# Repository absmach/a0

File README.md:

# 🔌 A0 Gateway

a0 is a modular **IoT gateway** built around the **ESP32-C6 (RISC-V)** platform, offering advanced wireless capabilities such as **Wi-Fi 6**, **Bluetooth 5**, and **802.15.4**. It supports multiple connectivity options including NB-IoT/LTE-M, WMBUS, and sub-GHz, enabling secure and scalable IoT deployments across smart buildings, industrial environments, and city infrastructure.

Optimized for low-power, battery-powered operation and modular expansion, A0 integrates secure communication, local storage, and multiple radio interfaces to serve as a versatile edge gateway in modern IoT ecosystems. While it includes support for Wireless and Wired M-Bus, its primary focus is on broad IoT connectivity and interoperability.

## 🌟 Features

- ⚙️ **RISC-V Architecture**: Powered by ESP32-C6 with a RISC-V core for efficiency and flexibility.
- 📡 **Advanced Wireless Connectivity**: Supports Wi-Fi 6, Bluetooth 5, and 802.15.4 for robust IoT networking.
- 🌐 **Multiple Uplink Options**: Provides NB-IoT/LTE-M for reliable data transmission.
- 🔋 **Battery-Powered Operation**: Optimized for low-power deployments with long-lasting battery support.
- 🔐 **Advanced Security**: Includes RSA-3072 secure boot, AES-128/256-XTS flash encryption, digital signature, HMAC identity protection, and hardware cryptographic accelerators for performance. Built-in Trusted Execution Environment (TEE) ensures secure software separation.
- 🛠️ **Modular Design**: Optional carrier boards adds NB-IoT/LTE-M, WMBUS, and sub-GHz radio support.
- 🔗 **Flexible IoT Connectivity**: Integrates with [Magistrala](https://github.com/absmach/magistrala) using multiple IoT protocols, including MQTT, CoAP, HTTP, and WebSockets.
- 🧩 **Zephyr RTOS Support**: Compatible with Zephyr for real-time, reliable IoT applications.
- 🖥️ **WebAssembly Runtime**: Runs lightweight, portable edge logic with WAMR (WebAssembly Micro Runtime).
- 🌀 **Propeller Orchestrator Integration**: Works with [Propeller](https://github.com/absmach/propeller) for secure, policy-driven orchestration of IoT workloads across the edge-cloud continuum.
- 📈 **Future-Ready for IoT Ecosystems**: Designed for interoperability in smart buildings, industrial IoT, and city-scale deployments.

## 🛠️ How It Works

1. **Connect & Collect**  
   Gather data from IoT sensors and devices via Wireless/Wired M-Bus, Wi-Fi, BLE, or sub-GHz radio.

2. **Process at the Edge**  
   Use the **ESP32-C6** for real-time processing or deploy **WebAssembly (Wasm)** modules with **WAMR** for flexible edge logic execution.

3. **Ensure Security**  
   Protect data and code integrity with **secure boot**, **flash encryption**, and **TEE-based isolation**, leveraging ESP32-C6 hardware security features.

4. **Transmit to IoT Platform**  
   Send processed data using **NB-IoT/LTE-M**, supporting multiple protocols (**MQTT**, **CoAP**, **HTTP**, **WebSockets**) for seamless integration with [**Magistrala**](https://github.com/absmach/magistrala).

5. **Orchestrate & Scale**  
   Integrate with the [**Propeller Orchestrator**](https://github.com/absmach/propeller) for policy-driven deployment and orchestration of workloads across the edge-cloud continuum.

6. **Manage Remotely**  
   Perform **OTA updates**, monitor device health, and manage configurations through connected IoT management tools.

## 📖 Documentation

For setup instructions, pinouts, and integration guides, see the full documentation:  
🔗 [A0 Documentation](https://www.absmach.eu/docs/hardware/s1-gateway/)

## 💡 Use Cases

- 🏢 **Smart Buildings**: Connect heat and water meters via Wireless M-Bus for real-time monitoring.
- 🏭 **Industrial IoT**: Collect and transmit sensor data in secure and bandwidth-constrained environments.
- 🌍 **Smart Cities**: Enable large-scale metering infrastructure with NB-IoT and sub-GHz connectivity.
- 🔐 **Secure Data Acquisition**: Ensure encrypted communication from edge devices to the cloud.

## 🔧 Hardware Highlights

The system consists of a **base board (A0)** with plug-in **expansion modules**:

- **A0 Base Board** ([a0/](a0/README.md)):
  - MCU: **ESP32-C6** module (RISC-V architecture)
  - Connectivity: **Wi-Fi 6**, **Bluetooth 5**, **IEEE 802.15.4**
  - Security: **Secure Boot**, **Flash Encryption**, **TEE**, Hardware Crypto Accelerators
  - Power: **USB-C**, external power supply, or **battery** (with charging support)
  - Expansion: **2 module slots — BUS1 and BUS2** — for plug-in connectivity modules

- **Expansion Modules** (plug into BUS1/BUS2):
  - [**SIM7080G**](modules/sim7080g/README.md): NB-IoT / LTE-M cellular uplink + GNSS
  - [**WMBUS**](modules/wmbus/README.md): Wireless M-Bus metering radio
  - [**E07-400M10S**](modules/E07400M10S/README.md): Sub-GHz radio module (400 MHz, 10 dBm)

## 🤝 Contributing

Contributions are welcome! Please check the [CONTRIBUTING.md](#) for details on how to get started.

## 📜 License

A0 is licensed under the **Apache-2.0 License**. See the [LICENSE](LICENSE) file for more details.

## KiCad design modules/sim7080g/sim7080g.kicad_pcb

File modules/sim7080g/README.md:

# SIM7080G Module

A plug-in expansion module for the [A0 base board](../../a0/README.md) based on the **SIMCom SIM7080G**.

## Overview

The SIM7080G provides **NB-IoT / LTE-M (Cat-M)** cellular connectivity plus **GNSS** positioning. Plug it into one of the A0 base board's expansion slots (**BUS1** or **BUS2**) to add a reliable cellular uplink for NB-IoT and LTE-M deployments.

## Key Features

- **Cellular**: NB-IoT and LTE-M (Cat-M) uplink
- **GNSS**: GPS/GLONASS/BeiDou/Galileo positioning
- **Interface**: connects to the ESP32-C6 over UART via the expansion bus
- **Power**: supplied from the expansion bus

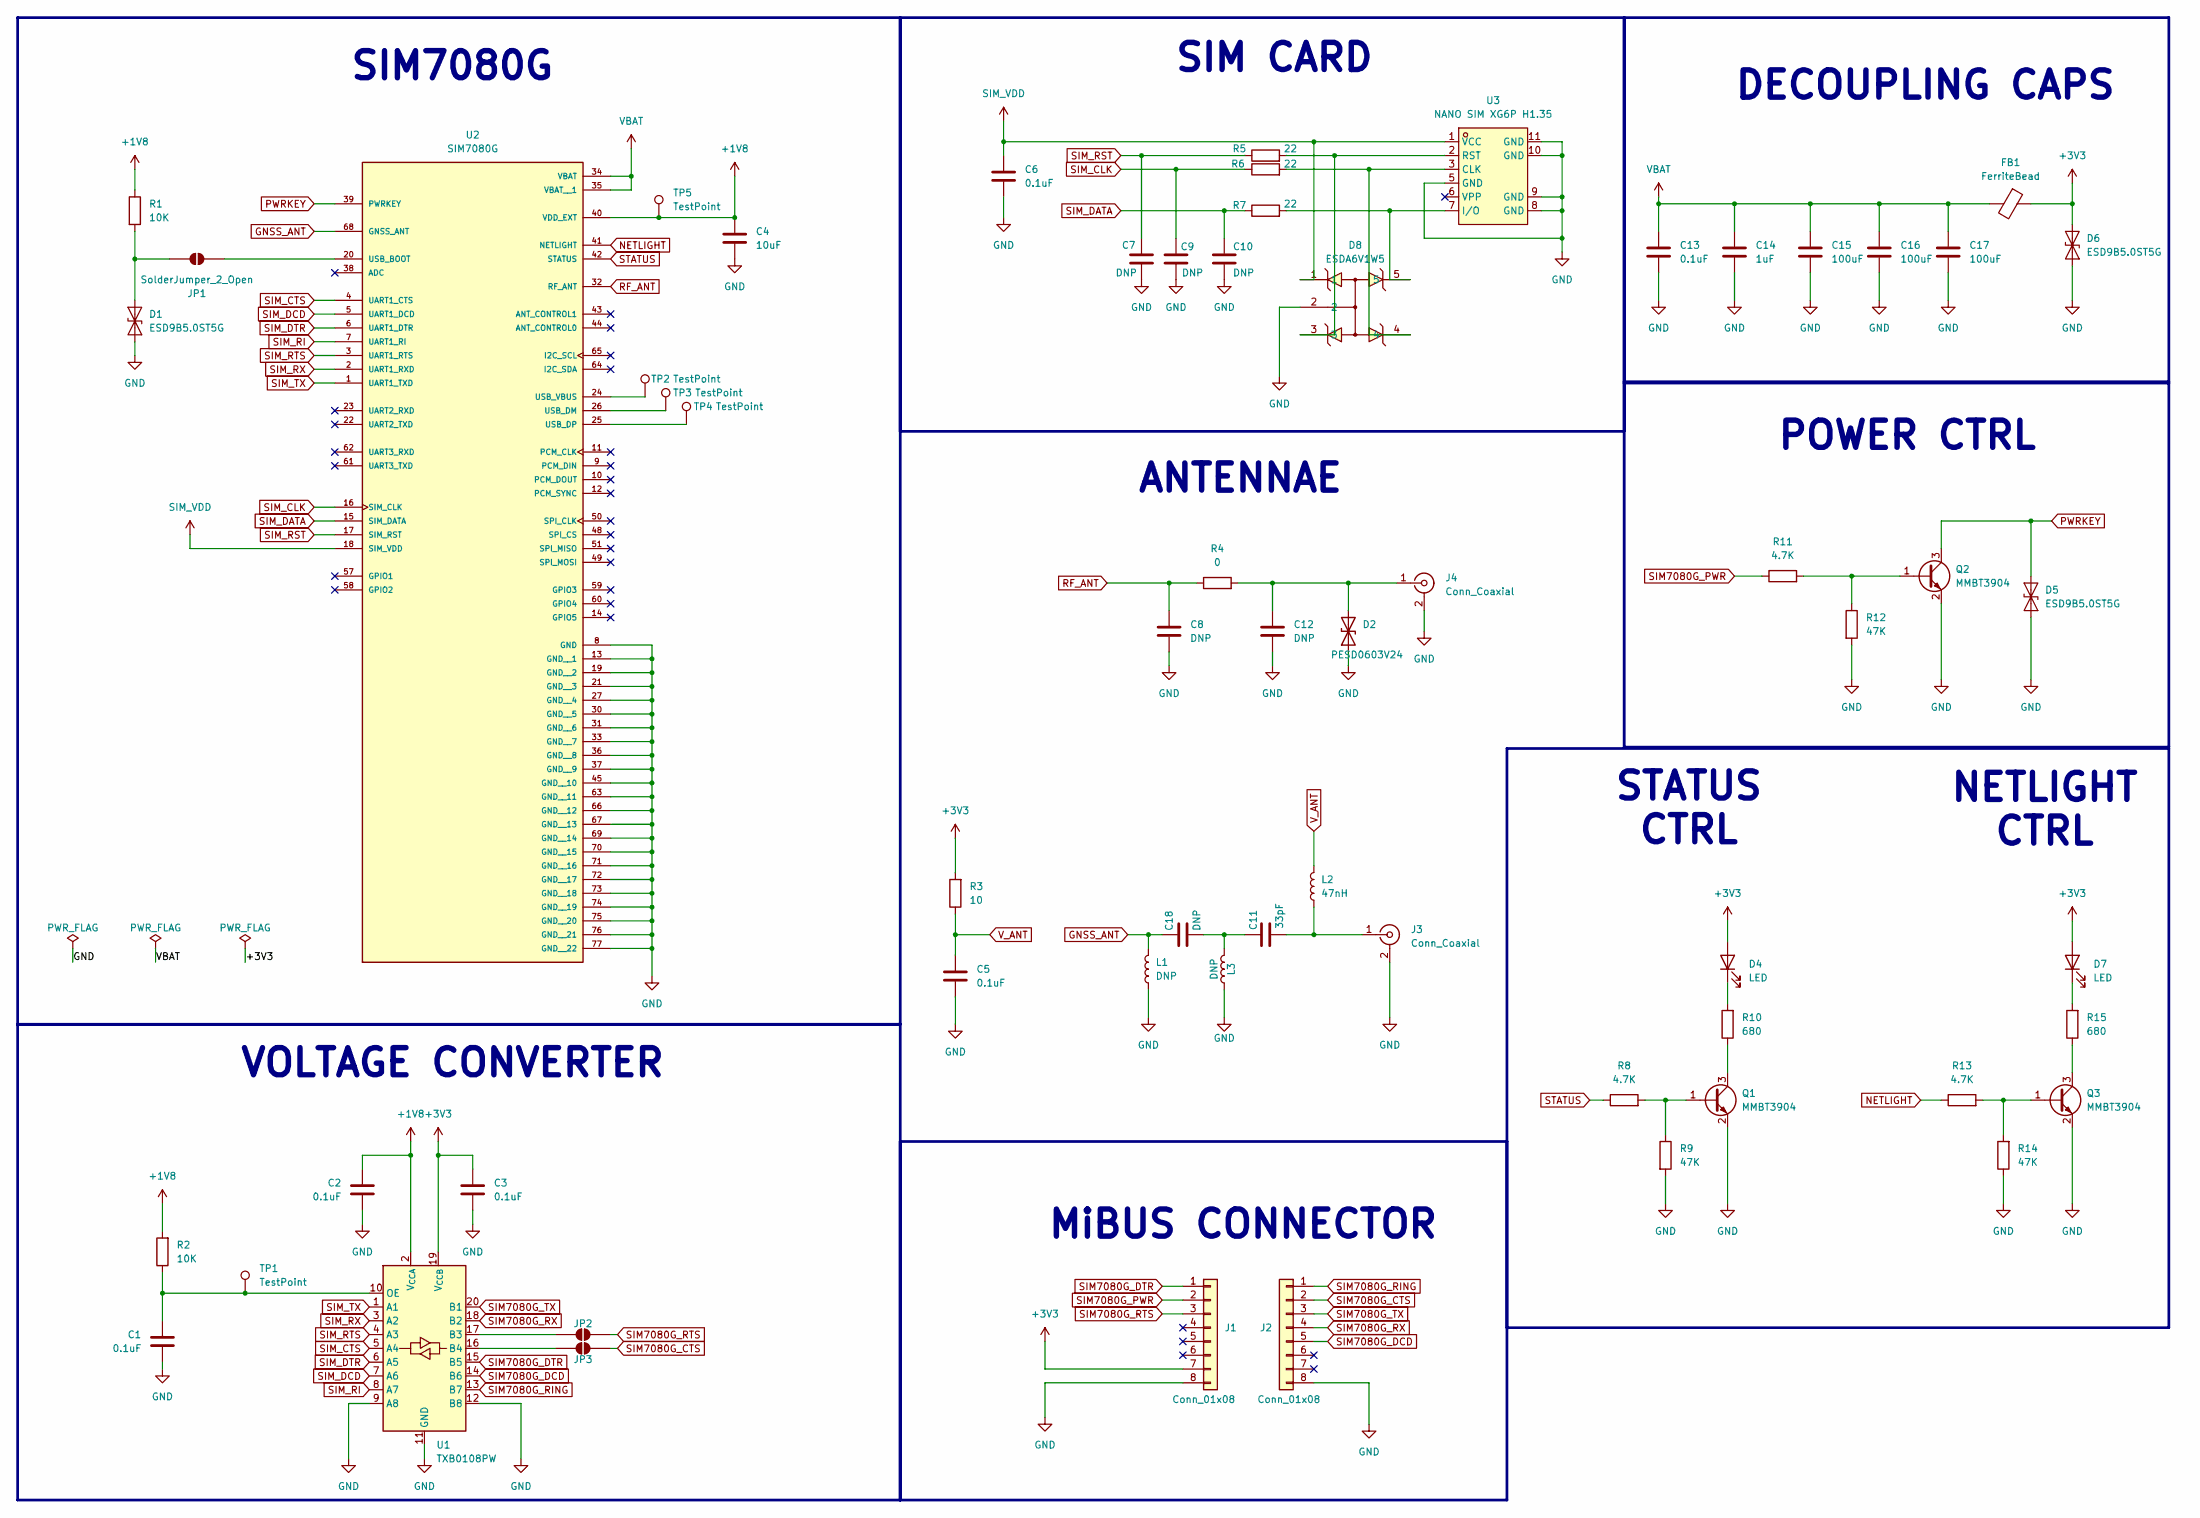
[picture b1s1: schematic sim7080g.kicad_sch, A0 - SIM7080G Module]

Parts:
C1, C2, C3, C5, C6, C13: 0.1uF; C_0805_2012Metric; JLCPCB C49678
C4: 10uF; C_0805_2012Metric; JLCPCB C15850
C7, C9, C10: DNP; C_0805_2012Metric; JLCPCB C1804
C8, C12: DNP; C_0402_1005Metric; JLCPCB C15008
C11: 33pF; C_0402_1005Metric; JLCPCB C1562
C14: 1uF; C_0805_2012Metric; JLCPCB C28323
C15, C16, C17: 100uF; C_1206_3216Metric; JLCPCB C15008
C18: DNP; C_0402_1005Metric
D1, D5, D6: ESD9B5.0ST5G; D_SOD-923; JLCPCB C111566
D2: PESD0603V24; D_0603_1608Metric; JLCPCB C19626259
D4, D7: LED; LED_0805_2012Metric; JLCPCB C965816
D8: ESDA6V1W5; C48677; MPN ESDA6V1W5; LCSC Part C48677
FB1: FerriteBead; L_0805_2012Metric; JLCPCB C56066
J1, J2: Conn_01x08; PinHeader_1x08_P2.54mm_Vertical; JLCPCB C492407
J3, J4: Conn_Coaxial; U.FL_Hirose_U.FL-R-SMT-1_Vertical; JLCPCB C88374
JP1, JP2, JP3: SolderJumper_2_Open; SolderJumper-2_P1.3mm_Open_RoundedPad1.0x1.5mm
L1, L3: DNP; L_0402_1005Metric
L2: 47nH; L_0402_1005Metric; JLCPCB C192855
Q1, Q2, Q3: MMBT3904; SOT-23; JLCPCB C20526
R1: 10K; R_0805_2012Metric; JLCPCB C17414
R2: 10K; R_0805_2012Metric; JLCPCB C17408
R3: 10; R_0805_2012Metric; JLCPCB C17415
R4: 0; R_0402_1005Metric; JLCPCB C17168
R5, R6, R7: 22; R_0805_2012Metric; JLCPCB C17561
R8, R11, R13: 4.7K; R_0805_2012Metric; JLCPCB C17673
R9, R12, R14: 47K; R_0805_2012Metric; JLCPCB C17713
R10, R15: 680; R_0805_2012Metric; JLCPCB C17798
TP1, TP2, TP3, TP4, TP5: TestPoint; TestPoint_Pad_1.0x1.0mm
U1: TXB0108PW; TSSOP-20_4.4x6.5mm_P0.65mm
U2: SIM7080G; PARTREV 1.04; JLCPCB C2943992
U3: NANO SIM XG6P H1.35; SIM-SMD_NANO-SIM; LCSC Part C7529386

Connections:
+1V8: C2.2, C4.2, R1.1, R2.2, TP5.1 (1_1), U1.2 (V_{CCA}), U2.40 (VDD_EXT)
+3V3: C3.2, D4.2 (A), D6.2 (A2), D7.2 (A), FB1.1, J1.7, R3.2, U1.19 (V_{CCB})
GND: C1.1, C2.1, C3.1, C4.1, C5.1, C6.1, C7.1, C8.2, C9.1, C10.1, C12.2, C13.1, C14.2, C15.2, C16.2, C17.2, D1.1 (A1), D2.1 (A1), D5.1 (A1), D6.1 (A1), D8.2, J1.8, J2.8, J3.2 (Ext), J4.2 (Ext), L1.1, L3.1, Q1.2 (E), Q2.2 (E), Q3.2 (E), R9.2, R12.2, R14.1, U1.9 (A8), U1.11 (GND), U1.12 (B8), U2.8 (GND), U2.13 (GND__1), U2.19 (GND__2), U2.21 (GND__3), U2.27 (GND__4), U2.30 (GND__5), U2.31 (GND__6), U2.33 (GND__7), U2.36 (GND__8), U2.37 (GND__9), U2.45 (GND__10), U2.63 (GND__11), U2.66 (GND__12), U2.67 (GND__13), U2.69 (GND__14), U2.70 (GND__15), U2.71 (GND__16), U2.72 (GND__17), U2.73 (GND__18), U2.74 (GND__19), U2.75 (GND__20), U2.76 (GND__21), U2.77 (GND__22), U3.5 (GND), U3.8 (GND), U3.9 (GND), U3.10 (GND), U3.11 (GND)
GNSS_ANT: C11.2, C18.1, C18.2, L1.2, L3.2, U2.68 (GNSS_ANT)
NETLIGHT: R13.1, U2.41 (NETLIGHT)
unnamed: D1.2 (A2), JP1.1 (A), R1.2
unnamed: C12.1, D2.2 (A2), J4.1 (In), R4.2
unnamed: D4.1 (K), R10.2
unnamed: D7.1 (K), R15.2
unnamed: C11.1, J3.1 (In), L2.1
unnamed: JP1.2 (B), U2.20 (USB_BOOT)
unnamed: JP2.1 (A), U1.17 (B3)
unnamed: JP3.1 (A), U1.16 (B4)
unnamed: Q1.1 (B), R8.2, R9.1
unnamed: Q1.3 (C), R10.1
unnamed: Q2.1 (B), R11.2, R12.1
unnamed: Q3.1 (B), R13.2, R14.2
unnamed: Q3.3 (C), R15.1
unnamed: C1.2, R2.1, TP1.1 (1_1), U1.10 (OE)
unnamed: TP3.1 (1_1), U2.26 (USB_DM)
unnamed: TP4.1 (1_1), U2.25 (USB_DP)
unnamed: TP2.1 (1_1), U2.24 (USB_VBUS)
unnamed: D8.4, R6.2, U3.3 (CLK)
unnamed: D8.5, R7.2, U3.7 (I/O)
unnamed: D8.3, R5.2, U3.2 (RST)
PWRKEY: D5.2 (A2), Q2.3 (C), U2.39 (PWRKEY)
RF_ANT: C8.1, R4.1, U2.32 (RF_ANT)
SIM7080G_CTS: J2.2, JP3.2 (B)
SIM7080G_DCD: J2.5, U1.14 (B6)
SIM7080G_DTR: J1.1, U1.15 (B5)
SIM7080G_PWR: J1.2, R11.1
SIM7080G_RING: J2.1, U1.13 (B7)
SIM7080G_RTS: J1.3, JP2.2 (B)
SIM7080G_RX: J2.4, U1.18 (B2)
SIM7080G_TX: J2.3, U1.20 (B1)
SIM_CLK: C9.2, R6.1, U2.16 (SIM_CLK)
SIM_CTS: U1.5 (A4), U2.4 (UART1_CTS)
SIM_DATA: C10.2, R7.1, U2.15 (SIM_DATA)
SIM_DCD: U1.7 (A6), U2.5 (UART1_DCD)
SIM_DTR: U1.6 (A5), U2.6 (UART1_DTR)
SIM_RI: U1.8 (A7), U2.7 (UART1_RI)
SIM_RST: C7.2, R5.1, U2.17 (SIM_RST)
SIM_RTS: U1.4 (A3), U2.3 (UART1_RTS)
SIM_RX: U1.3 (A2), U2.2 (UART1_RXD)
SIM_TX: U1.1 (A1), U2.1 (UART1_TXD)
SIM_VDD: C6.2, D8.1, U2.18 (SIM_VDD), U3.1 (VCC)
STATUS: R8.1, U2.42 (STATUS)
VBAT: C13.2, C14.1, C15.1, C16.1, C17.1, FB1.2, U2.34 (VBAT), U2.35 (VBAT__1)
V_ANT: C5.2, L2.2, R3.1

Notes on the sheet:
VOLTAGE CONVERTER
DECOUPLING CAPS
SIM CARD
SIM7080G
ANTENNAE
STATUS CTRL
NETLIGHT CTRL
MiBUS CONNECTOR
POWER CTRL

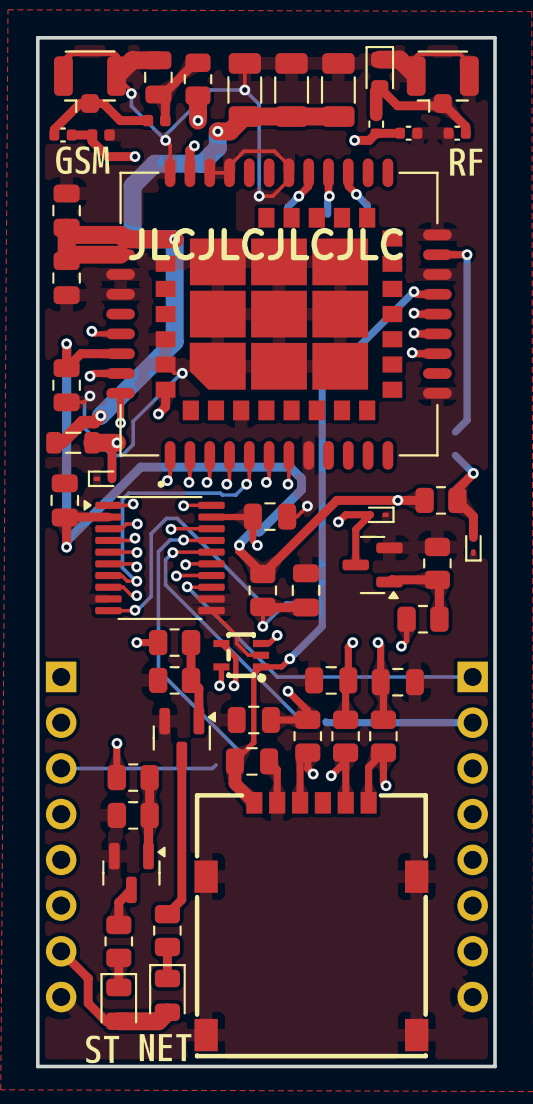
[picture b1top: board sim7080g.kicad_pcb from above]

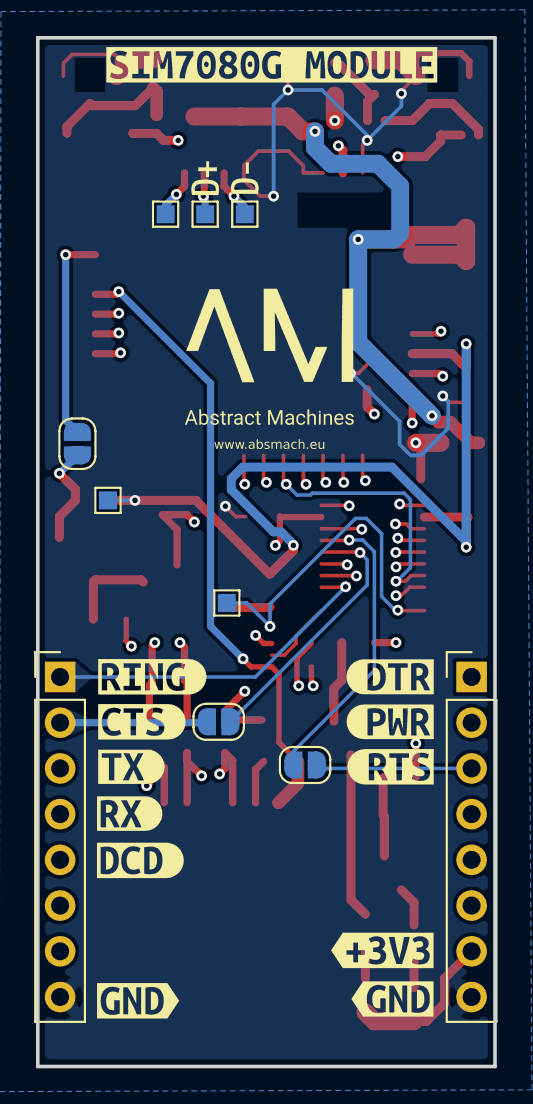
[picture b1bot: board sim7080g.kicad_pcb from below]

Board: 4 copper layers, 25.4 x 57.2 mm, 78 parts (24 on the bottom side), 49 nets.

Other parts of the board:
kibuzzard-6A58AA2C: G***; kibuzzard-6A58AA2C
kibuzzard-6A58AA08: G***; kibuzzard-6A58AA08
kibuzzard-6A58AA80: G***; kibuzzard-6A58AA80
kibuzzard-6A58AA90: G***; kibuzzard-6A58AA90
kibuzzard-6A58AAA8: G***; kibuzzard-6A58AAA8
kibuzzard-6A58AAC0: G***; kibuzzard-6A58AAC0
kibuzzard-6A58AAD1: G***; kibuzzard-6A58AAD1
kibuzzard-6A58ABB3: G***; kibuzzard-6A58ABB3
kibuzzard-6A58ABC2: G***; kibuzzard-6A58ABC2
kibuzzard-6A58ABCC: G***; kibuzzard-6A58ABCC
kibuzzard-6A58ABD9: G***; kibuzzard-6A58ABD9
kibuzzard-6A58ABE5: G***; kibuzzard-6A58ABE5
kibuzzard-6A58ADF5: G***; kibuzzard-6A58ADF5
kibuzzard-6AA2AF52: G***; kibuzzard-6AA2AF52
kibuzzard-6AA2C0AA: G***; kibuzzard-6AA2C0AA
kibuzzard-6AA2C081: G***; kibuzzard-6AA2C081
kibuzzard-6AA2C170: G***; kibuzzard-6AA2C170
kibuzzard-6AA2C182: G***; kibuzzard-6AA2C182

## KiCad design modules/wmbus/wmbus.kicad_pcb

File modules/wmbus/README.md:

# WMBUS Module

A plug-in expansion module for the [A0 base board](../../a0/README.md) implementing **Wireless M-Bus (EN 13757-4)**.

## Overview

The WMBUS module adds a Wireless M-Bus radio for reading utility meters (heat, water, gas, electricity). Plug it into one of the A0 base board's expansion slots (**BUS1** or **BUS2**) to enable smart metering deployments.

## Key Features

- **Wireless M-Bus (EN 13757-4)** communication
- Connects to the ESP32-C6 over the expansion bus
- Powered from the expansion bus

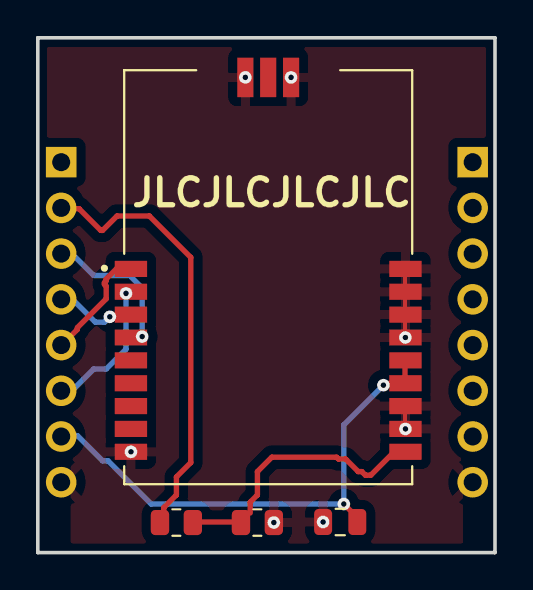
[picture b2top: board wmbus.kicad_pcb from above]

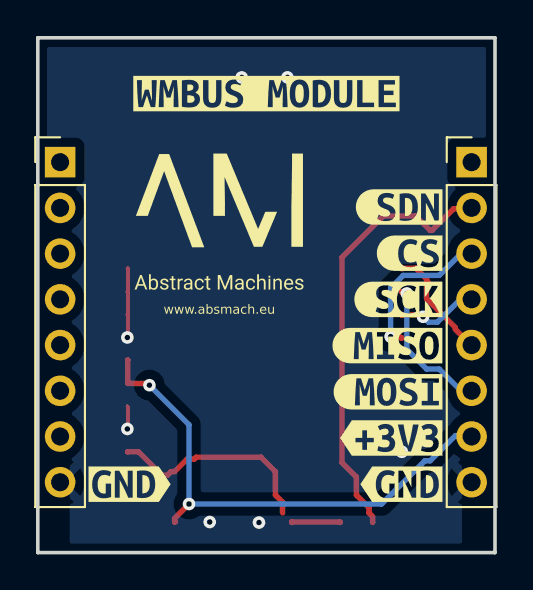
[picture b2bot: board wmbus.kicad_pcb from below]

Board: 2 copper layers, 25.4 x 28.6 mm, 15 parts (11 on the bottom side), 8 nets.

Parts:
C1: 0.1uF; C_0805_2012Metric
J1, J2: Conn_01x08; PinHeader_1x08_P2.54mm_Vertical
R1: 100; R_0805_2012Metric
R2: 10K; R_0805_2012Metric
U2: RC-S2LP-868
kibuzzard-6A563B7D: G***; kibuzzard-6A563B7D
kibuzzard-6A563B31: G***; kibuzzard-6A563B31
kibuzzard-6A563B41: G***; kibuzzard-6A563B41
kibuzzard-6A563B50: G***; kibuzzard-6A563B50
kibuzzard-6A563B65: G***; kibuzzard-6A563B65
kibuzzard-6A563B71: G***; kibuzzard-6A563B71
kibuzzard-6A563B88: G***; kibuzzard-6A563B88
kibuzzard-6A563B96: G***; kibuzzard-6A563B96
kibuzzard-6A563BEF: G***; kibuzzard-6A563BEF

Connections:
+3V3: C1.1, J1.7, U2.13 (VCC), U2.14 (VCC)
CS: J1.3, U2.4 (CSN)
GND: C1.2, J1.8, J2.8, R2.2, U2.9 (GND), U2.11 (GND), U2.12 (GND), U2.15 (GND), U2.16 (GND), U2.17 (GND), U2.18 (GND), U2.19 (GND), U2.21 (GND)
MISO: J1.5, U2.1 (SDO)
MOSI: J1.6, U2.2 (SDI)
unnamed: R1.2, R2.1, U2.10 (SDN)
SCK: J1.4, U2.3 (SCLK)
SDN: J1.2, R1.1

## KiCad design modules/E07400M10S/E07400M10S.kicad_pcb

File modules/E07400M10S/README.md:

# E07-400M10S Module

A plug-in expansion module for the [A0 base board](../../a0/README.md) based on the **Ebyte E07-400M10S** sub-GHz radio module.

## Overview

The E07-400M10S is a compact sub-GHz (400 MHz) RF transceiver module with 10 dBm output. Plug it into one of the A0 base board's expansion slots (**BUS1** or **BUS2**) to add low-power, long-range sub-GHz connectivity for private sensor networks and IEEE 802.15.4-style links.

## Key Features

- **Sub-GHz radio**: 400 MHz band, 10 dBm output power
- **Low power**: suited to battery-powered operation
- **Interface**: SPI / UART over the expansion bus
- **Power**: supplied from the expansion bus

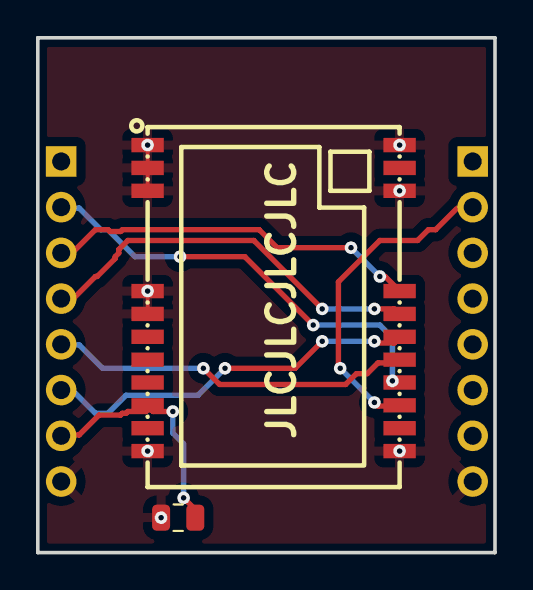
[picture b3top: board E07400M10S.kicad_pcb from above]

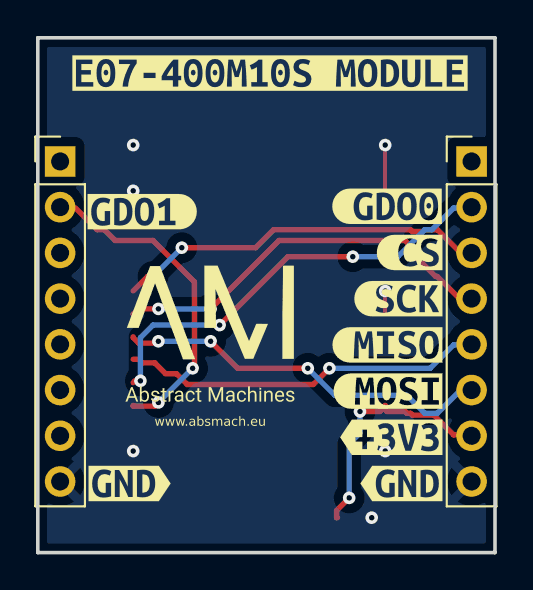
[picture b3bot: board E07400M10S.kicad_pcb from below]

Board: 2 copper layers, 25.4 x 28.6 mm, 14 parts (12 on the bottom side), 8 nets.

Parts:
C1: 0.1uF; C_0805_2012Metric
J1, J2: Conn_01x08; PinHeader_1x08_P2.54mm_Vertical
U1: E07-400M10S; C2965513
kibuzzard-6A5A4D23: G***; kibuzzard-6A5A4D23
kibuzzard-6A5A4D79: G***; kibuzzard-6A5A4D79
kibuzzard-6A5A4D90: G***; kibuzzard-6A5A4D90
kibuzzard-6A563B7D: G***; kibuzzard-6A563B7D
kibuzzard-6A563B41: G***; kibuzzard-6A563B41
kibuzzard-6A563B50: G***; kibuzzard-6A563B50
kibuzzard-6A563B65: G***; kibuzzard-6A563B65
kibuzzard-6A563B71: G***; kibuzzard-6A563B71
kibuzzard-6A563B88: G***; kibuzzard-6A563B88
kibuzzard-6A563B96: G***; kibuzzard-6A563B96

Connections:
+3V3: C1.1, J1.7, U1.9 (VCC)
CS: J1.3, U1.19 (CSN)
GDO0: J1.2, U1.15 (GD00)
GDO1: J2.2, U1.14 (GD02)
GND: C1.2, J1.8, J2.8, U1.1 (GND), U1.2 (GND), U1.3 (GND), U1.4 (GND), U1.5 (GND), U1.11 (GND), U1.12 (GND), U1.20 (GND), U1.22 (GND)
MISO: J1.5, U1.16 (MISO/GD01)
MOSI: J1.6, U1.17 (MOSI)
SCK: J1.4, U1.18 (SCK)

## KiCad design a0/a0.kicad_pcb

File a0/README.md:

# A0 Base Board

**A0** is the base board of the modular A0 IoT gateway, built around an **ESP32-C6 module** (RISC-V, Wi-Fi 6, Bluetooth 5, IEEE 802.15.4).

## About the ESP32-C6

The ESP32-C6 is Espressif's first Wi-Fi 6 SoC, integrating **2.4 GHz Wi-Fi 6 (802.11ax)**, **Bluetooth 5 (LE)** and **IEEE 802.15.4** (Thread/Zigbee) radio connectivity in a single low-power chip ([product page](https://www.espressif.com/en/products/socs/esp32-c6)).

| Spec            | Details                                                                                                                                                                                                                                                        |
| --------------- | -------------------------------------------------------------------------------------------------------------------------------------------------------------------------------------------------------------------------------------------------------------- |
| **CPU**         | High-performance 32-bit RISC-V core, up to **160 MHz**, plus a low-power (LP) 32-bit RISC-V core, up to **20 MHz**                                                                                                                                             |
| **Memory**      | 320 KB ROM, 512 KB SRAM, external flash                                                                                                                                                                                                                        |
| **Wireless**    | 2.4 GHz Wi-Fi 6 (802.11ax, 20 MHz) with 802.11 b/g/n (20/40 MHz) backward compatibility; OFDMA up/downlink, downlink MU-MIMO, Target Wake Time (TWT); Bluetooth 5 LE with coded PHY long-range and 2 Mbps high-throughput PHY; IEEE 802.15.4 for Thread/Zigbee |
| **GPIO**        | 30 (QFN40) or 22 (QFN32) programmable GPIOs                                                                                                                                                                                                                    |
| **Peripherals** | SPI, UART, I2C, I2S, RMT, TWAI, PWM, SDIO, Motor Control PWM, 12-bit ADC, temperature sensor                                                                                                                                                                   |
| **Security**    | RSA-3072 secure boot, AES-128/256-XTS flash encryption, digital signature and HMAC peripherals, hardware cryptographic accelerators, Trusted Execution Environment (TEE) for privilege/software separation                                                     |
| **Software**    | Open-source ESP-IDF; ESP-Hosted / ESP-AT for co-processor use; ESP RainMaker; Zephyr support                                                                                                                                                                   |

Wi-Fi 6 features (OFDMA, MU-MIMO, TWT) deliver low latency and long battery life even in congested RF environments, while combined Wi-Fi + BLE + 802.15.4 support makes it a natural fit for Matter end-point devices, Thread Border Routers, and Zigbee bridges.

## Overview

A0 provides everything needed to power and run the gateway, while pushing all radio/cellular connectivity onto removable expansion modules:

- **ESP32-C6 module on top** — main compute + Wi-Fi/BLE/802.15.4 connectivity, with hardware secure boot, flash encryption, and a TEE.
- **Power**:
  - USB-C power input
  - External power supply input
  - Battery support (with charging)
- **Expansion**: two module slots, **BUS1** and **BUS2**, where any of the following modules can be plugged in:
  - [SIM7080G](../modules/sim7080g/README.md) — NB-IoT/LTE-M cellular + GNSS
  - [WMBUS](../modules/wmbus/README.md) — Wireless M-Bus radio
  - [E07-400M10S](../modules/E07400M10S/README.md) — Sub-GHz radio (400 MHz, 10 dBm)

## Manufacturing

Gerber and assembly outputs are in [`jlcpcb/`](jlcpcb/) (`gerber/` and `production_files/`).

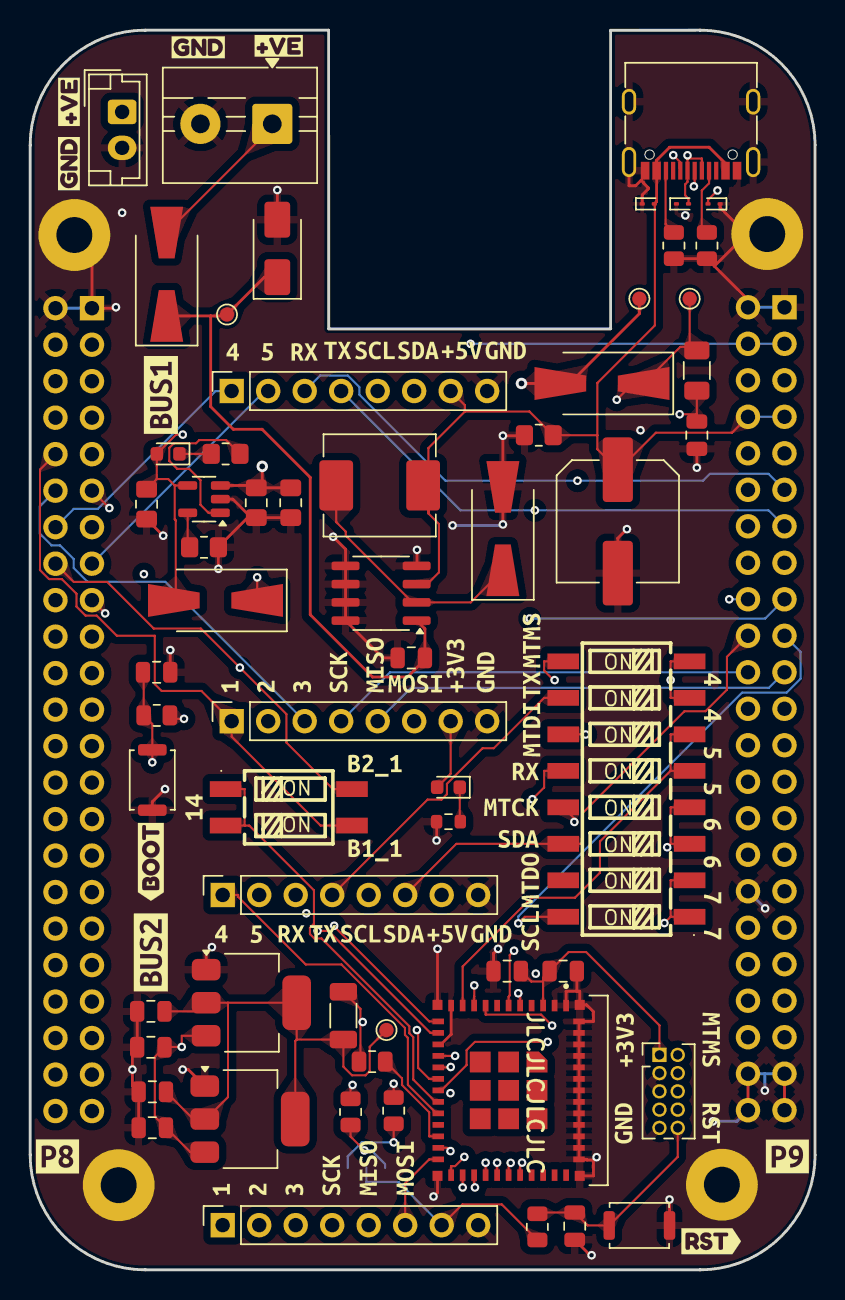
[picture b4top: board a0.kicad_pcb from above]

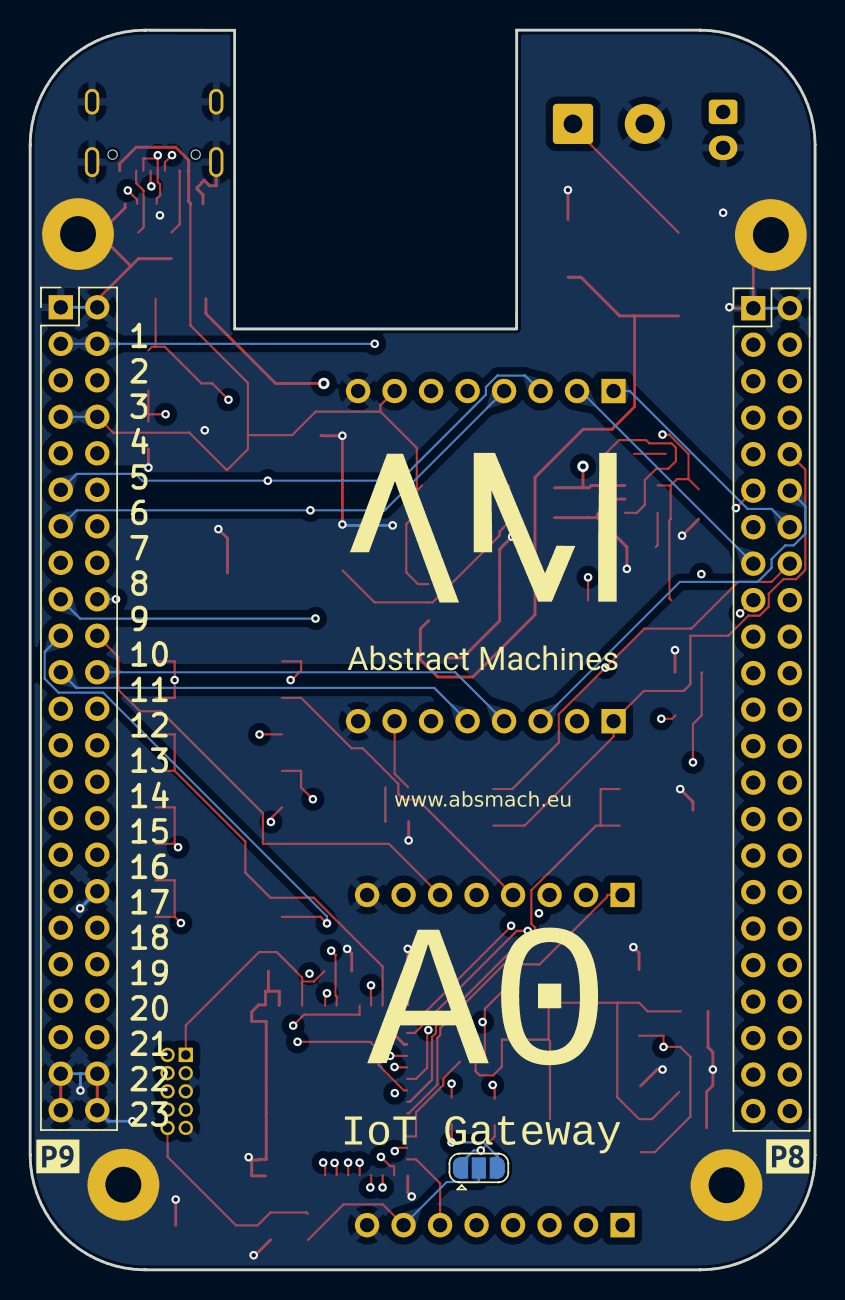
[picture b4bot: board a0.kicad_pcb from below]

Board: 4 copper layers, 54.6 x 86.3 mm, 131 parts (5 on the bottom side), 50 nets.

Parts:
C1, C2: 1uF; C_0805_2012Metric
C3: 22uF; C_0805_2012Metric
C4, C10, C11: 0.1uF; C_0805_2012Metric
C5, C6, C7: 4.7uF; C_0805_2012Metric_Pad1.18x1.45mm_HandSolder
C8, C9, C12, C13: 10uF; C_0805_2012Metric
C14: 330uF; C_Elec_8x10.2
D1, D7, D8, D9: 40V 3A 550mV@3A Schottky; D_SMA-SMB_Universal_Handsoldering
D2, D3, D4: ESD9B5.0ST5G; D_SOD-923
D5: BZV55C27; D_SMA
D6, D10: LED; LED_0603_1608Metric
F1: Fuse; Fuse_1206_3216Metric
FB1: FerriteBead; L_1206_3216Metric_Pad1.22x1.90mm_HandSolder
H1, H2, H3, H4: MountingHole_Pad; MountingHole_2.5mm_Pad
J1, J2, J3, J4: Conn_01x08; PinSocket_1x08_P2.54mm_Vertical
J5: Beagle P8; PinHeader_2x23_P2.54mm_Vertical
J6: Beagle P9; PinHeader_2x23_P2.54mm_Vertical
J7: ESP32 USB; USB_C_Receptacle_G-Switch_GT-USB-7010ASV
J8: Screw_Terminal_01x02; TerminalBlock_MaiXu_MX126-5.0-02P_1x02_P5.00mm
J9: BAT_JST_01x02; JST_EH_B2B-EH-A_1x02_P2.50mm_Vertical
J10: Conn_ARM_JTAG_SWD_10; PinHeader_2x05_P1.27mm_Vertical
JP1: SolderJumper_3_Open; SolderJumper-3_P1.3mm_Open_RoundedPad1.0x1.5mm
L1: 47uH/2A; L_Chilisin_BMRB00060624
R1, R4, R5: 10K; R_0805_2012Metric
R2, R3: 2.2K; R_0805_2012Metric
R6, R7: 5K1; R_0805_2012Metric
R8: 2k; R_0805_2012Metric_Pad1.20x1.40mm_HandSolder
R9: 220; R_0805_2012Metric_Pad1.20x1.40mm_HandSolder
R10: 10k; R_0805_2012Metric_Pad1.20x1.40mm_HandSolder
R11: 220; R_0603_1608Metric
SW1, SW2: SW_Push; SW_Push_SPST_NO_Alps_SKRK
SW5: SMXS-08K-TP; C5439767
TP1, TP2, TP3, TP4: TestPoint; TestPoint_Pad_D1.0mm
U1: SMXS-02K-TP; C5439761
U4: ESP32-C6-MINI-1/U; XCVR_ESP32-C3-MINI-1U-N4
U5: MCP73831-2-OT; SOT-23-5
U6: XL1509-5.0; SOIC-8_3.9x4.9mm_P1.27mm
U7, U8: AMS1117-3.3; SOT-223-3_TabPin2
kibuzzard-6A55FB86, kibuzzard-6A55FB8650: G***; kibuzzard-6A55FB86
kibuzzard-6A55FB93, kibuzzard-6A55FB9349: G***; kibuzzard-6A55FB93
kibuzzard-6A55FC6E7: G***; kibuzzard-6A55FC6E
kibuzzard-6A55FC8415: G***; kibuzzard-6A55FC84
kibuzzard-6A55FD1132: G***; kibuzzard-6A55FD11
kibuzzard-6A55FD3129: G***; kibuzzard-6A55FD31
kibuzzard-6A55FD6527: G***; kibuzzard-6A55FD65
kibuzzard-6A55FD7025: G***; kibuzzard-6A55FD70
kibuzzard-6A55FE0F26: G***; kibuzzard-6A55FE0F
kibuzzard-6A55FE7B11: G***; kibuzzard-6A55FE7B
kibuzzard-6A55FE1730: G***; kibuzzard-6A55FE17
kibuzzard-6A55FE2828: G***; kibuzzard-6A55FE28
kibuzzard-6A55FE3524: G***; kibuzzard-6A55FE35
kibuzzard-6A55FE7212: G***; kibuzzard-6A55FE72
kibuzzard-6A55FE9913: G***; kibuzzard-6A55FE99
kibuzzard-6A55FEAA10: G***; kibuzzard-6A55FEAA
kibuzzard-6A55FFC232: G***; kibuzzard-6A55FFC2
kibuzzard-6A55FFC933: G***; kibuzzard-6A55FFC9
kibuzzard-6A55FFCE34: G***; kibuzzard-6A55FFCE
kibuzzard-6A55FFD235: G***; kibuzzard-6A55FFD2
kibuzzard-6A55FFD736: G***; kibuzzard-6A55FFD7
kibuzzard-6A55FFDB37: G***; kibuzzard-6A55FFDB
kibuzzard-6A55FFDF38: G***; kibuzzard-6A55FFDF
kibuzzard-6A55FFE439: G***; kibuzzard-6A55FFE4
kibuzzard-6A5604D22: G***; kibuzzard-6A5604D2
kibuzzard-6A5604E99: G***; kibuzzard-6A5604E9
kibuzzard-6A56002C: G***; kibuzzard-6A56002C
kibuzzard-6A56005A: G***; kibuzzard-6A56005A
kibuzzard-6A56010B2, kibuzzard-6A56010B41: G***; kibuzzard-6A56010B
kibuzzard-6A56011A4, kibuzzard-6A56011A43: G***; kibuzzard-6A56011A
kibuzzard-6A56012F5, kibuzzard-6A56012F44: G***; kibuzzard-6A56012F
kibuzzard-6A56013C46: G***; kibuzzard-6A56013C
kibuzzard-6A56014C, kibuzzard-6A56014C19: G***; kibuzzard-6A56014C
kibuzzard-6A56016F, kibuzzard-6A56016F17: G***; kibuzzard-6A56016F
kibuzzard-6A56043E14: G***; kibuzzard-6A56043E
kibuzzard-6A56059C1: G***; kibuzzard-6A56059C
kibuzzard-6A560036: G***; kibuzzard-6A560036
kibuzzard-6A560120, kibuzzard-6A56012020: G***; kibuzzard-6A560120
kibuzzard-6A560129, kibuzzard-6A56012921: G***; kibuzzard-6A560129
kibuzzard-6A560142, kibuzzard-6A56014223, kibuzzard-6A56014247: G***; kibuzzard-6A560142
kibuzzard-6A560146, kibuzzard-6A56014618: G***; kibuzzard-6A560146
kibuzzard-6A560169, kibuzzard-6A56016916: G***; kibuzzard-6A560169
kibuzzard-6A560175, kibuzzard-6A56017522: G***; kibuzzard-6A560175
kibuzzard-6A5601031, kibuzzard-6A56010340: G***; kibuzzard-6A560103
kibuzzard-6A5601133, kibuzzard-6A56011342: G***; kibuzzard-6A560113
kibuzzard-6A5601356, kibuzzard-6A56013545: G***; kibuzzard-6A560135
kibuzzard-6A5605438: G***; kibuzzard-6A560543
kibuzzard-6A56041948: G***; kibuzzard-6A560419

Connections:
+3V3: C3.1, C4.1, D10.2 (A), FB1.2, J1.7, J4.7, J6.3, J6.4, J10.1 (VTref), JP1.2 (C), R1.1, R4.1, R5.1, U4.3 (3V3)
FB_5V: C5.1, C14.1, D2.2 (A2), D6.2 (A), D8.2 (A), J2.7, J3.7, J6.7, J6.8, J7.A4 (VBUS), J7.A9 (VBUS), J7.B4 (VBUS), J7.B9 (VBUS), L1.2, R10.2, U5.4 (V_{DD}), U6.3 (FB)
GND: C1.2, C2.2, C3.2, C4.2, C5.2, C6.2, C7.2, C8.2, C9.2, C10.2, C11.2, C12.2, C13.2, C14.2, D2.1 (A1), D3.1 (A1), D4.1 (A1), D5.2 (A), D9.2 (A), H1.1, H2.1, H3.1, H4.1, J1.8, J2.8, J3.8, J4.8, J5.1, J5.2, J6.1, J6.2, J6.34, J6.43, J6.44, J6.45, J6.46, J7.A1 (GND), J7.A12 (GND), J7.B1 (GND), J7.B12 (GND), J7.S1 (SHIELD), J8.2, J9.2, J10.3 (GND), J10.5 (GND), J10.9 (GNDDetect), R6.2, R7.2, R8.1, R10.1, R11.2, SW1.1, SW2.1, U4.1 (GND), U4.2 (GND), U4.11 (GND), U4.14 (GND), U4.36 (GND), U4.37 (GND), U4.38 (GND), U4.39 (GND), U4.40 (GND), U4.41 (GND), U4.42 (GND), U4.43 (GND), U4.44 (GND), U4.45 (GND), U4.46 (GND), U4.47 (GND), U4.48 (GND), U4.50 (GND), U4.51 (GND), U4.52 (GND), U4.53 (GND), U5.2 (V_{SS}), U6.4 (~EN), U6.5 (GND), U6.6 (GND), U6.7 (GND), U6.8 (GND), U7.1 (GND), U8.1 (GND)
GPIO4: SW5.7, SW5.8, U4.9 (MTMS/GPIO4/ADC1_CH4)
GPIO5: SW5.5, SW5.6, U4.10 (MTDI/GPIO5/ADC1_CH5)
GPIO6: SW5.3, SW5.4, U4.15 (MTCK/GPIO6/ADC1_CH6)
GPIO7: SW5.1, SW5.2, U4.16 (MTDO/GPIO7)
GPIO8: R5.2, U4.22 (GPIO8)
GPIO9: C2.1, R4.2, SW2.2, U4.23 (GPIO9)
GPIO14: U1.1, U1.2, U4.19 (GPIO14)
MCU_RST: C1.1, J10.10 (~RESET), R1.2, SW1.2, U4.8 (EN/CHIP_PU)
MISO: J1.5, J4.5, J6.21, U4.25 (GPIO19)
MOSI: J1.6, J4.6, J6.18, U4.24 (GPIO18)
MTCK: J10.4 (SWCLK/TCK), SW5.13
MTDI: J10.8 (NC/TDI), SW5.11
MTMS: J10.2 (SWDIO/TMS), SW5.9
MiBUS1_1: J1.1, J5.10, U1.3
MiBUS1_2: J1.2, J5.11, U4.13 (GPIO1/ADC1_CH1/XTAL_32K_N)
MiBUS1_3: J1.3, J5.12, U4.5 (GPIO2/ADC1_CH2)
MiBUS1_4: J3.1, J5.14, U4.6 (GPIO3/ADC1_CH3)
MiBUS1_5: J3.2, J5.15, U4.12 (GPIO0/ADC1_CH0/XTAL_32K_P)
MiBUS1_RX: J3.3, J6.11, U4.31 (U0TXD/GPIO16)
MiBUS1_TX: J3.4, J6.13, U4.30 (U0RXD/GPIO17)
MiBUS2_1: J4.1, J5.16, U1.4
MiBUS2_2: J4.2, J5.17, U4.28 (GPIO22)
MiBUS2_3: J4.3, J6.17, U4.27 (GPIO21)
MiBUS2_4: J2.1, U4.20 (GPIO15)
MiBUS2_5: J2.2, U4.29 (GPIO23)
MiBUS2_RX: J2.3, SW5.12
MiBUS2_TX: J2.4, SW5.10
unnamed: D1.2 (A), J8.1
unnamed: D6.1 (K), R9.1
unnamed: D7.1 (K), D8.1 (K), F1.1, TP3.1
unnamed: D9.1 (K), L1.1, U6.2 (OUT)
unnamed: D10.1 (K), R11.1
unnamed: J7.A5 (CC1), R7.1
unnamed: J7.B5 (CC2), R6.1
unnamed: JP1.1 (A), R3.1
unnamed: JP1.3 (B), R2.2
unnamed: R8.2, U5.5 (PROG)
unnamed: R9.2, U5.1 (STAT)
unnamed: C9.1, C10.1, C11.1, F1.2, U7.3 (VI), U8.3 (VI)
unnamed: C12.1, C13.1, FB1.1, TP4.1, U7.2 (VO), U8.2 (VO)
SCK: J1.4, J4.4, J6.22, U4.26 (GPIO20)
SCL: J2.5, J3.5, J6.19, R3.2, SW5.16
SDA: J2.6, J3.6, J6.20, R2.1, SW5.14
USB_D+: D4.2 (A2), J7.A6 (D+), J7.B6 (D+), U4.18 (GPIO13/USB_D+)
USB_D-: D3.2 (A2), J7.A7 (D-), J7.B7 (D-), U4.17 (GPIO12/USB_D-)
VBAT: C6.1, C7.1, D7.2 (A), J9.1, TP2.1, U5.3 (V_{BAT})
VIN: C8.1, D1.1 (K), D5.1 (K), TP1.1, U6.1 (VIN)

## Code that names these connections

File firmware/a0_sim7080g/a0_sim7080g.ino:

// A0 (ESP32-C6) <-> SIM7080G module, stacked on MiBUS1 (J1/J3).
// Pinout verified from a0/a0.kicad_sch and modules/sim7080g/sim7080g.kicad_sch netlists.
//
// MiBUS1 pin | ESP32-C6  | SIM7080G module
// -----------|-----------|------------------
// J1-1       | GPIO14 *  | DTR
// J1-2       | GPIO1     | PWRKEY
// J1-3       | GPIO2     | RTS
// J1-7 / J3-8| +3V3 / GND| VCC / GND
// J3-1       | GPIO3     | RING
// J3-2       | GPIO0     | CTS
// J3-3       | GPIO16    | TX  (modem TX -> ESP32 RX)
// J3-4       | GPIO17    | RX  (ESP32 TX -> modem RX)
//
// * GPIO14 reaches MiBUS1 through the U1 (SMXS-02K-TP) slide switch on A0 —
//   it must be set to the MiBUS1 side, not MiBUS2, or DTR will float.
//
// RTS/CTS (GPIO2/GPIO0) are left unused here — they need a solder jumper on
// the module to be connected at all, so touching those pins does nothing.
// DTR (GPIO14) is also left unused — the modem ignores it until AT+CSCLK=1
// is set, which we never do here, so it has no effect at power-on defaults.

#define MODEM_RX_PIN   16  // ESP32 RX  <- SIM7080G TX
#define MODEM_TX_PIN   17  // ESP32 TX  -> SIM7080G RX
#define MODEM_PWRKEY   1

#define MODEM_BAUD     115200

HardwareSerial Modem(1);

void modemPowerOn() {
  // GPIO1 does not drive the modem's real PWRKEY pin directly — on the
  // module PCB it drives NPN transistor Q2 (base via R8, base pulled to GND
  // by R11), whose collector is the actual PWRKEY pin (U2/39). That inverts
  // the signal: GPIO1 HIGH turns Q2 on and pulls PWRKEY low (asserted);
  // GPIO1 LOW releases it back high (idle). This also toggles power rather
  // than setting an absolute level — if the modem was already on, this
  // pulse turns it OFF instead.
  //
  // Per SIMCom spec: PWRKEY low >1.0s turns ON, low >1.2s turns OFF. 1100ms
  // sits inside that ON-only window with margin on both sides — a pulse at
  // or above 1200ms risks toggling an already-on modem back off instead.
  pinMode(MODEM_PWRKEY, OUTPUT);
  digitalWrite(MODEM_PWRKEY, LOW);   // idle (PWRKEY released/high)
  delay(100);
  digitalWrite(MODEM_PWRKEY, HIGH);  // assert (PWRKEY pulled low)
  delay(1100);
  digitalWrite(MODEM_PWRKEY, LOW);   // release
  delay(4500);  // SIM7080G needs ~4-5s before UART/RDY comes up
}

String modemSendAT(const String &cmd, unsigned long timeoutMs = 2000) {
  while (Modem.available()) Modem.read();
  Modem.print(cmd);
  Modem.print("\r\n");

  String reply;
  unsigned long start = millis();
  while (millis() - start < timeoutMs) {
    while (Modem.available()) reply += (char)Modem.read();
    if (reply.indexOf("OK") != -1 || reply.indexOf("ERROR") != -1) break;
  }
  return reply;
}

// SIM7080G needs a few "AT" pulses to autobaud-sync before it replies.
bool modemWaitReady(uint8_t attempts = 10) {
  for (uint8_t i = 0; i < attempts; i++) {
    String reply = modemSendAT("AT", 1000);
    if (reply.indexOf("OK") != -1) return true;
    delay(500);
  }
  return false;
}

void setup() {
  Serial.begin(115200);

  Modem.begin(MODEM_BAUD, SERIAL_8N1, MODEM_RX_PIN, MODEM_TX_PIN);

  Serial.println("Powering on SIM7080G...");
  modemPowerOn();

  if (!modemWaitReady()) {
    Serial.println("Modem did not respond to AT — check power/PWRKEY toggle state and wiring.");
    return;
  }
  Serial.println("Modem is up.");
  Serial.println(modemSendAT("ATI"));
  Serial.println(modemSendAT("AT+CSQ"));
}

void loop() {
  // AT passthrough: type commands in the Serial Monitor, they go to the
  // modem. Send "PWR" to re-pulse PWRKEY by hand (e.g. if the modem powered
  // off instead of on) without reflashing.
  if (Serial.available()) {
    String cmd = Serial.readStringUntil('\n');
    cmd.trim();
    if (cmd.equalsIgnoreCase("PWR")) {
      Serial.println("Pulsing PWRKEY...");
      modemPowerOn();
      Serial.println(modemWaitReady() ? "Modem is up." : "Still no response.");
    } else if (cmd.length() > 0) {
      Serial.println(modemSendAT(cmd));
    }
  }
  while (Modem.available()) {
    Serial.write(Modem.read());
  }
}
